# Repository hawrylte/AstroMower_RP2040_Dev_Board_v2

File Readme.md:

# AstroMower RP2040 Dev Board v2
## About
RP2040 Development Board to explore programming capability of Raspberry Pi [RP2040](https://www.raspberrypi.com/products/rp2040/) MCU for use in future projects.

## Hardware
  * 2 Layer PCB with parts populated on both sides

  * Spacing of pin headers is 0.9" to use on standard breadboard.

  * PCB Overall Dimensions 1.05" W X 1.95" L

  * USB-C Interface

  * Resistor and Capacitor sizes are 0603 and 0805 with hand solder footprints

  * Incorporates Neopixel addressable LED

  * 8 MB QSPI Flash

  * All parts ordered through Digi-Key

  * Developed in [KiCad 7.0](https://www.kicad.org/)

  * DRC for Manufacture through [OSHPARK](https://oshpark.com/)

## Software
### ***SOFTWARE UNDER DEVELOPMENT***
### MicroPython
MicroPython firmware for board can be downloaded directly or built from source.

***Instructions for building from source on Debian based system***

Building from source requires MicroPython source. Installation of this mirrors instructions found in Raspberry Pi [Raspberry Pi Pico Python SDK](https://datasheets.raspberrypi.com/pico/raspberry-pi-pico-python-sdk.pdf)

Create *pico* directory
```
mkdir pico
cd pico
```
Then clone the *micropython* git repository
```
git clone https://github.com/micropython/micropython.git --branch master
```
Fetch additional submodules required for a RP2 MCU board
```
cd micropython
make -C port/rp2 submodules
```
To build *micropython* additional tools are required
```
sudo apt update
sudo apt install cmake gcc-arm-none-eabi libnewlib-arm-none-eabi build-essential libstdc++-arm-none-eabi-newlib
```
Bootstrap a special tool for MicroPython builds
```
make -C mpy-cross
```
***Load Board Specific Files for AstroMower Board***

Download *AstroMower RP2040 Dev Board v2* git repository
```
cd ..
git clone https://github.com/hawrylte/AstroMower_RP2040_Dev_Board_v2.git
```
Move specific board files to proper locations in *MicroPython* source files
```
cp -r AstroMower_RP2040_Dev_Board_v2/src/ASTROMOWER_RP2040_DEV_BOARD_V2 micropython/ports/rp2/boards/ASTROMOWER_RP2040_DEV_BOARD_V2
cp -r AstroMower_RP2040_Dev_Board_v2/src/astromower_rp2040_dev_board_v2.h micropython/lib/pico-sdk/src/boards/include/boards/astromower_rp2040_dev_board_v2.h
```
Build the port we need for RP2040 and specify our particular board to be built
```
cd micropython/ports/rp2
make BOARD=ASTROMOWER_RP2040_DEV_BOARD_V2
```
Copy UF2 Firmware from *MicroPython* build directory to *pico* directory
```
cd ../../..
cp micropython/ports/rp2/build-ASTROMOWER_RP2040_DEV_BOARD_V2/firmware.uf2 AstroMower_RP2040_Dev_Board_MicroPython_firmware.uf2
```
### C/C++

***Instructions for setting up PICO-SDK from source on Debian based system***

Setting up the *pico-sdk* mirrors instructions found in Raspberry Pi [Gettting Stated with Raspberry Pi Pico](https://datasheets.raspberrypi.com/pico/getting-started-with-pico.pdf)

Create *pico* directory
```
mkdir pico
cd pico
```
Then clone the *pico-sdk* and the *pico-examples* git repositories
```
git clone http://github.com/raspberrypi/pico-sdk.git --branch master
cd pico-sdk
git submodule update --init
cd ..
git clone http://github.com/raspberrypi/pico-examples.git --branch master
```
To build *pico-examples* additional tools are required
```
sudo apt update
sudo apt install cmake gcc-arm-none-eabi libnewlib-arm-none-eabi build-essentials libstdc++-arm-none-eabi-newlib
```
Download *AstroMower RP2040 Dev Board v2* git repositiry
```
git clone https://github.com/hawrylte/AstroMower_RP2040_Dev_Board_v2.git
```
Move specific board files to proper locations in *pico-sdk* source files
```
cp -r AstroMower_RP2040_Dev_Board_v2/src/astromower_rp2040_dev_board_v2.h pico-sdk/src/boards/include/boards/astromower_rp2040_dev_board_v2.h
```
***Instructions for building Blink example from PICO-EXAMPLES from source on Debian based system***

***AstroMower Dev Board v2 does not have a discrete LED for Blink to run, but this shows the process of building a C/C++ program for the AstroMower Dev Board v2***

Change to *pico-examples* directory and make *build* directory.
```
cd pico-examples
mkdir build
cd buid
```
Set *PICO_SDK_PATH*
```
export PICO-SDK-PATH=../../pico-sdk
```
Prepare cmke build directory and identify board to build program for.
```
cmake .. -DPICO_BOARD=astromower_rp2040_dev_board_v2
cd blink
make -j4
```
*blink.elf* is used by the debugger
*blink.uf2* is the program and can be dragged onto the RP2040 USB Mass Storage Device

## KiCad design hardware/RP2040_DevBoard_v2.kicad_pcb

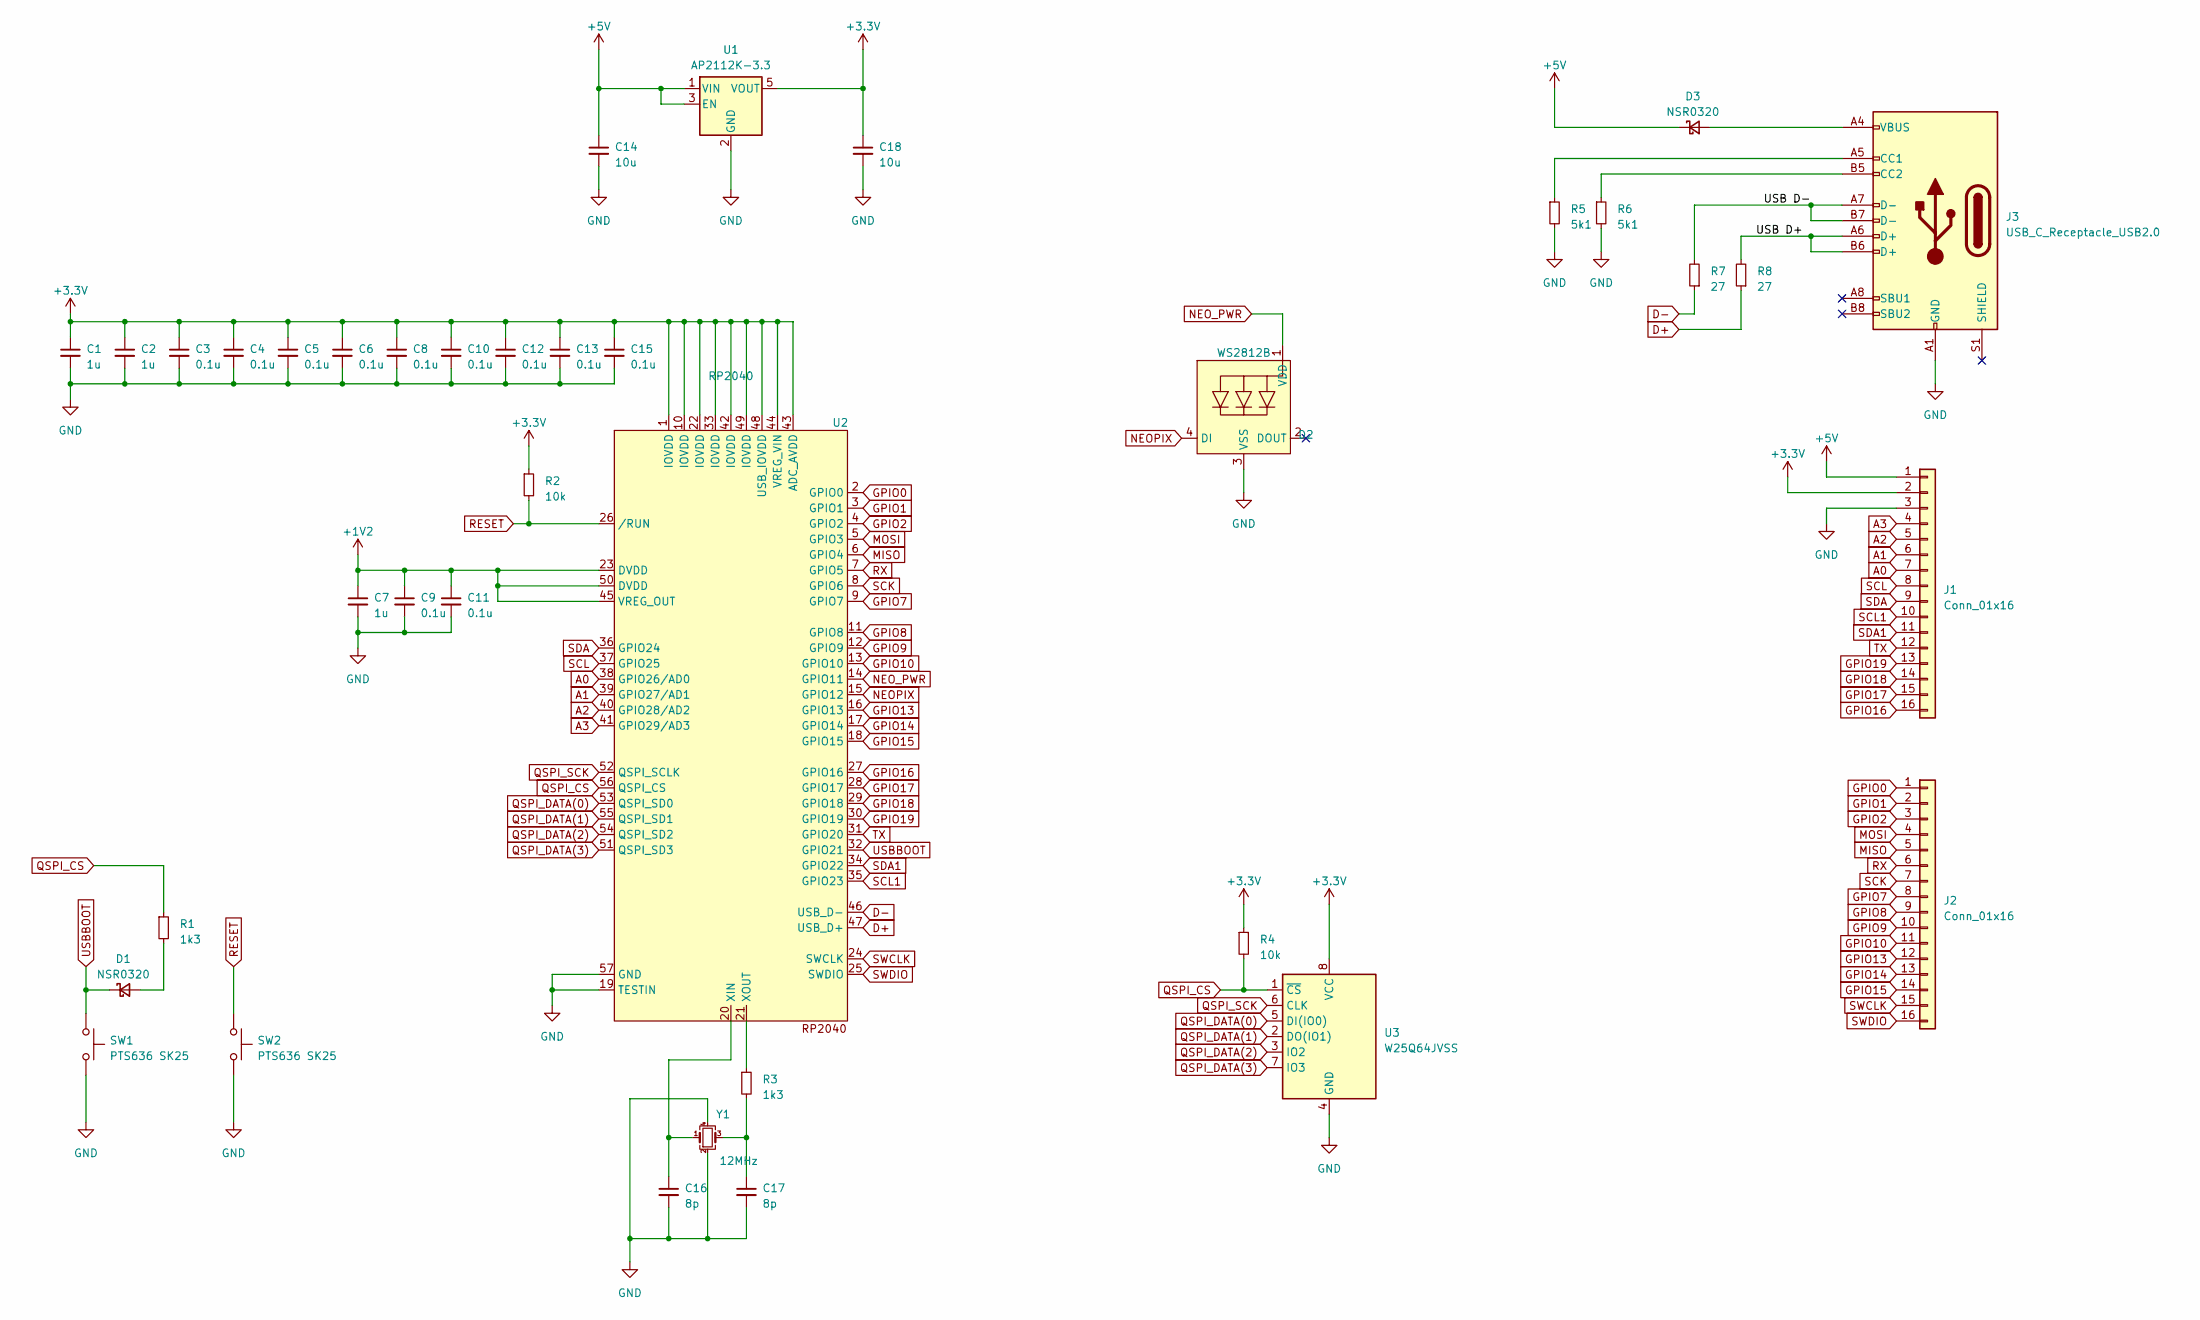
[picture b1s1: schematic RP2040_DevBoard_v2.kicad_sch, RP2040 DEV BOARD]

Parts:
C1, C2, C7: 1u; C_0603_1608Metric_Pad1.08x0.95mm_HandSolder; Mfg PN 0603YC105KAT2A; Digi-Key PN 478-5010-2-ND
C3, C4, C5, C6, C8, C9, C10, C11, C12, C13, C15: 0.1u; C_0603_1608Metric_Pad1.08x0.95mm_HandSolder; Mfg PN 06033C104KAT4A; Digi-Key PN 478-7018-2-ND
C14, C18: 10u; C_0805_2012Metric_Pad1.18x1.45mm_HandSolder; Mfg PN 0805ZC106KAT2A; Digi-Key PN 478-10578-2-ND
C16, C17: 8p; C_0603_1608Metric_Pad1.08x0.95mm_HandSolder; Mfg PN 06031A8R0D4T2A; Digi-Key PN 478-9370-2-ND
D1, D3: NSR0320; D_SOD-323_HandSoldering; Mfg PN NSR0320MW2T3G; Digi-Key PN NSR0320MW2T3GOSTR-ND
D2: WS2812B; Mfg PN COM-16347; Digi-Key PN 1568-COM-16347TR-ND
J1, J2: Conn_01x16; PinHeader_1x16_P2.54mm_Vertical; Mfg PN PH1-16-UA; Digi-Key PN 2057-PH1-16-UA-ND
J3: USB_C_Receptacle_USB2.0; USB_C_Receptacle_GCT_USB4105-xx-A_16P_TopMnt_Horizontal; Mfg PN USB4105-GF-A; Digi-Key PN 2073-USB4105-GF-ATR-ND
R1, R3: 1k3; R_0603_1608Metric_Pad0.98x0.95mm_HandSolder; Mfg PN ERJ-3EKF1301V; Digi-Key PN P1.30KHTR-ND
R2, R4: 10k; R_0603_1608Metric_Pad0.98x0.95mm_HandSolder; Mfg PN ERJ-3EKF1002V; Digi-Key PN P10.0KHTR-ND
R5, R6: 5k1; R_0603_1608Metric_Pad0.98x0.95mm_HandSolder; Mfg PN ERJ-3EKF5101V; Digi-Key PN P5.10KHTR-ND
R7, R8: 27; R_0603_1608Metric_Pad0.98x0.95mm_HandSolder; Mfg PN ERJ-3EKF27R0V; Digi-Key PN P27.0HTR-ND
SW1, SW2: PTS636 SK25; SW_SPST_CK_RS282G05A3; Mfg PN PTS636 SK25 SMTR LFS; Digi-Key PN CKN12322-2-ND
U1: AP2112K-3.3; SOT-23-5; Mfg PN AP2112K-3.3TRG1; Digi-Key PN AP2112K-3.3TRG1DITR-ND
U2: RP2040; QFN-56-1EP_7x7mm_P0.4mm_EP4x4mm; Mfg PN SC0914(13); Digi-Key PN 2648-SC0914(13)TR-ND
U3: W25Q64JVSS; SOIC-8_5.23x5.23mm_P1.27mm; Mfg PN W25Q64JVSSIQ; Digi-Key PN W25Q64JVSSIQ-ND
Y1: 12MHz; Crystal_SMD_3225-4Pin_3.2x2.5mm_HandSoldering; Mfg PN 830108206909; Digi-Key PN 1923-830108206909TR-ND

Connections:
+1V2: C7.1, C9.1, C11.1, U2.23 (DVDD), U2.45 (VREG_OUT), U2.50 (DVDD)
+3.3V: C1.1, C2.1, C3.1, C4.1, C5.1, C6.1, C8.1, C10.1, C12.1, C13.1, C15.1, C18.1, J1.2, R2.1, R4.1, U1.5 (VOUT), U2.1 (IOVDD), U2.10 (IOVDD), U2.22 (IOVDD), U2.33 (IOVDD), U2.42 (IOVDD), U2.43 (ADC_AVDD), U2.44 (VREG_VIN), U2.48 (USB_IOVDD), U2.49 (IOVDD), U3.8 (VCC)
+5V: C14.1, D3.1 (K), J1.1, U1.1 (VIN), U1.3 (EN)
/USB D+: J3.A6 (D+), J3.B6 (D+), R8.2
/USB D-: J3.A7 (D-), J3.B7 (D-), R7.2
A0: J1.7, U2.38 (GPIO26/AD0)
A1: J1.6, U2.39 (GPIO27/AD1)
A2: J1.5, U2.40 (GPIO28/AD2)
A3: J1.4, U2.41 (GPIO29/AD3)
D+: R8.1, U2.47 (USB_D+)
D-: R7.1, U2.46 (USB_D-)
GND: C1.2, C2.2, C3.2, C4.2, C5.2, C6.2, C7.2, C8.2, C9.2, C10.2, C11.2, C12.2, C13.2, C14.2, C15.2, C16.2, C17.2, C18.2, D2.3 (VSS), J1.3, J3.A1 (GND), J3.A12 (GND), J3.B1 (GND), J3.B12 (GND), R5.2, R6.2, SW1.2 (B), SW2.2 (B), U1.2 (GND), U2.19 (TESTIN), U2.57 (GND), U3.4 (GND), Y1.2, Y1.4
GPIO0: J2.1, U2.2 (GPIO0)
GPIO1: J2.2, U2.3 (GPIO1)
GPIO2: J2.3, U2.4 (GPIO2)
GPIO7: J2.8, U2.9 (GPIO7)
GPIO8: J2.9, U2.11 (GPIO8)
GPIO9: J2.10, U2.12 (GPIO9)
GPIO10: J2.11, U2.13 (GPIO10)
GPIO13: J2.12, U2.16 (GPIO13)
GPIO14: J2.13, U2.17 (GPIO14)
GPIO15: J2.14, U2.18 (GPIO15)
GPIO16: J1.16, U2.27 (GPIO16)
GPIO17: J1.15, U2.28 (GPIO17)
GPIO18: J1.14, U2.29 (GPIO18)
GPIO19: J1.13, U2.30 (GPIO19)
MISO: J2.5, U2.6 (GPIO4)
MOSI: J2.4, U2.5 (GPIO3)
NEOPIX: D2.4 (DI), U2.15 (GPIO12)
NEO_PWR: D2.1 (VDD), U2.14 (GPIO11)
unnamed: C17.1, R3.2, Y1.3
unnamed: D1.2 (A), R1.2
unnamed: D3.2 (A), J3.A4 (VBUS), J3.A9 (VBUS), J3.B4 (VBUS), J3.B9 (VBUS)
unnamed: J3.A5 (CC1), R5.1
unnamed: J3.B5 (CC2), R6.1
unnamed: C16.1, U2.20 (XIN), Y1.1
unnamed: R3.1, U2.21 (XOUT)
QSPI_CS: R1.1, R4.2, U2.56 (QSPI_CS), U3.1 (~CS)
QSPI_DATA(0): U2.53 (QSPI_SD0), U3.5 (DI(IO0))
QSPI_DATA(1): U2.55 (QSPI_SD1), U3.2 (DO(IO1))
QSPI_DATA(2): U2.54 (QSPI_SD2), U3.3 (IO2)
QSPI_DATA(3): U2.51 (QSPI_SD3), U3.7 (IO3)
QSPI_SCK: U2.52 (QSPI_SCLK), U3.6 (CLK)
RESET: R2.2, SW2.1 (A), U2.26 (/RUN)
RX: J2.6, U2.7 (GPIO5)
SCK: J2.7, U2.8 (GPIO6)
SCL: J1.8, U2.37 (GPIO25)
SCL1: J1.10, U2.35 (GPIO23)
SDA: J1.9, U2.36 (GPIO24)
SDA1: J1.11, U2.34 (GPIO22)
SWCLK: J2.15, U2.24 (SWCLK)
SWDIO: J2.16, U2.25 (SWDIO)
TX: J1.12, U2.31 (GPIO20)
USBBOOT: D1.1 (K), SW1.1 (A), U2.32 (GPIO21)

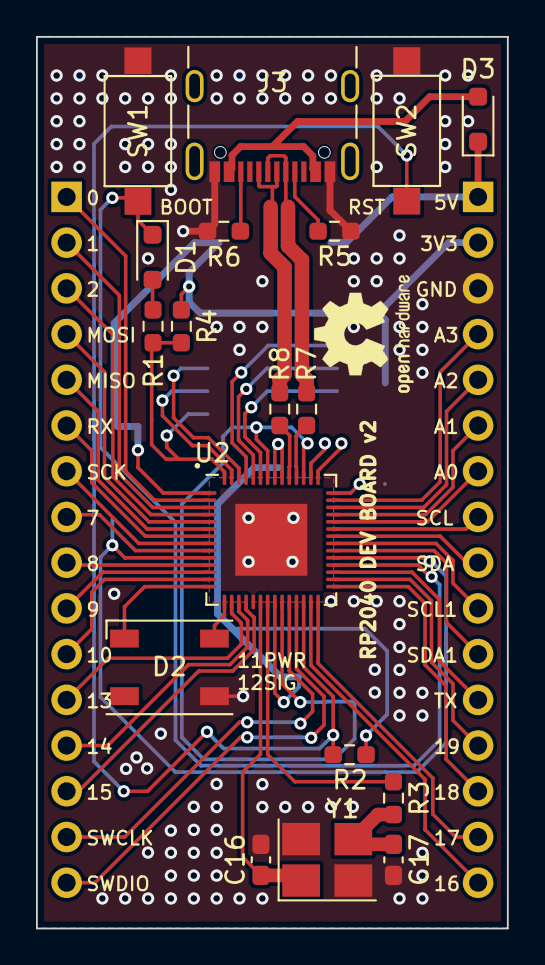
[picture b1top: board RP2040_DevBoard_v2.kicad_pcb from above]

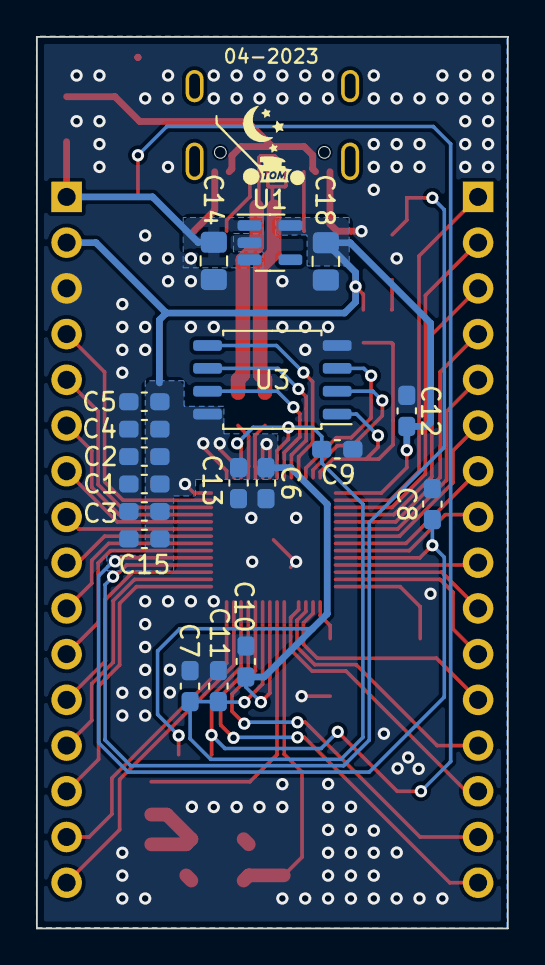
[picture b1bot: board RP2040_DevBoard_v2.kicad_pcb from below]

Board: 2 copper layers, 26.2 x 49.5 mm, 38 parts (20 on the bottom side), 54 nets.

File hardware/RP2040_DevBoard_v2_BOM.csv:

"Copyright 2023 Thomas Hawrylik","","","","","",""
"This source describes Open Hardware and is licensed under the CERN-OHL-S v2 or any later version","","","","","",""
"You may redistribute and modify this source and make products using it under the terms of the CERN-OHL-S v2 (https://ohwr.org/cern ohl s v2.txt).","","","","","",""
"This source is distributed WITHOUT ANY EXPRESS OR IMPLIED WARRANTY, INCLUDING OF MERCHANTABILITY, SATISFACTORY QUALITY AND FITNESS FOR A PARTICULAR PURPOSE.","","","","","",""
"Please see the CERN-OHL-S v2 for applicable conditions.","","","","","",""
"Reference","Value","Footprint","Datasheet","Digi-Key PN","Mfg PN","Qty"
"C1, C2, C7","1u","Capacitor_SMD:C_0603_1608Metric_Pad1.08x0.95mm_HandSolder","https://datasheets.kyocera-avx.com/X7RDielectric.pdf","478-5010-2-ND","0603YC105KAT2A","3"
"C3-C6, C8-C13, C15","0.1u","Capacitor_SMD:C_0603_1608Metric_Pad1.08x0.95mm_HandSolder","https://datasheets.kyocera-avx.com/X7RDielectric.pdf","478-7018-2-ND","06033C104KAT4A","11"
"C14, C18","10u","Capacitor_SMD:C_0805_2012Metric_Pad1.18x1.45mm_HandSolder","https://datasheets.kyocera-avx.com/X7RDielectric.pdf","478-10578-2-ND","0805ZC106KAT2A","2"
"C16, C17","8p","Capacitor_SMD:C_0603_1608Metric_Pad1.08x0.95mm_HandSolder","https://datasheets.kyocera-avx.com/AutoMLCC.pdf","478-9370-2-ND","06031A8R0D4T2A","2"
"D1, D3","NSR0320","Diode_SMD:D_SOD-323_HandSoldering","https://www.onsemi.com/pdf/datasheet/nsr0320mw2t1-d.pdf","NSR0320MW2T3GOSTR-ND","NSR0320MW2T3G","2"
"D2","WS2812B","RP2040_DevBoard:WS2812B","http://cdn.sparkfun.com/datasheets/BreakoutBoards/WS2812B.pdf","1568-COM-16347TR-ND","COM-16347","1"
"J1, J2","Conn_01x16","Connector_PinHeader_2.54mm:PinHeader_1x16_P2.54mm_Vertical","https://app.adam-tech.com/products/download/data_sheet/20160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","2057-PH1-16-UA-ND","PH1-16-UA","2"
"J3","USB_C_Receptacle_USB2.0","Connector_USB:USB_C_Receptacle_GCT_USB4105-xx-A_16P_TopMnt_Horizontal","https://media.digikey.com/pdf/Data%20Sheets/GCT%20PDFs/USB41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","2073-USB4105-GF-ATR-ND","USB4105-GF-A","1"
"R1, R3","1k3","Resistor_SMD:R_0603_1608Metric_Pad0.98x0.95mm_HandSolder","https://industrial.panasonic.com/cdbs/www-data/pdf/RDA0000/A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","P1.30KHTR-ND","ERJ-3EKF1301V","2"
"R2, R4","10k","Resistor_SMD:R_0603_1608Metric_Pad0.98x0.95mm_HandSolder","https://industrial.panasonic.com/cdbs/www-data/pdf/RDA0000/A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","P10.0KHTR-ND","ERJ-3EKF1002V","2"
"R5, R6","5k1","Resistor_SMD:R_0603_1608Metric_Pad0.98x0.95mm_HandSolder","https://industrial.panasonic.com/cdbs/www-data/pdf/RDA0000/A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","P5.10KHTR-ND","ERJ-3EKF5101V","2"
"R7, R8","27","Resistor_SMD:R_0603_1608Metric_Pad0.98x0.95mm_HandSolder","https://industrial.panasonic.com/cdbs/www-data/pdf/RDA0000/A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","P27.0HTR-ND","ERJ-3EKF27R0V","2"
"SW1, SW2","PTS636 SK25","Button_Switch_SMD:SW_SPST_CK_RS282G05A3","https://www.ckswitches.com/media/2779/pts636.pdf","CKN12322-2-ND","PTS636 SK25 SMTR LFS","2"
"U1","AP2112K-3.3","Package_TO_SOT_SMD:SOT-23-5","https://www.diodes.com/assets/Datasheets/AP2112.pdf","AP2112K-3.3TRG1DITR-ND","AP2112K-3.3TRG1","1"
"U2","RP2040","Package_DFN_QFN:QFN-56-1EP_7x7mm_P0.4mm_EP4x4mm","https://datasheets.raspberrypi.com/rp2040/rp2040-datasheet.pdf","2648-SC0914(13)TR-ND","SC0914(13)","1"
"U3","W25Q64JVSS","Package_SO:SOIC-8_5.23x5.23mm_P1.27mm","https://www.winbond.com/resource-files/w25q64jv%20revj%20032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","W25Q64JVSSIQ-ND","W25Q64JVSSIQ","1"
"Y1","12MHz","Crystal:Crystal_SMD_3225-4Pin_3.2x2.5mm_HandSoldering","https://www.we-online.com/catalog/datasheet/830108206909.pdf","1923-830108206909TR-ND","830108206909","1"

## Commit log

2023-05-04 Create license.txt
    CERN OHL v2 Strongly Reciprocal
2023-05-04 Rename RP2040_DevBoard.bak to RP2040_DevBoard.bak
2023-05-04 Rename WS2812B.kicad_mod to WS2812B.kicad_mod
2023-05-04 Rename RP2040_DevBoard.kicad_sym to RP2040_DevBoard.kicad_sym
2023-05-04 Rename RP2040_DevBoard_v2.kicad_pcb to RP2040_DevBoard_v2.kicad_pcb
2023-05-04 Rename RP2040_DevBoard_v2.kicad_prl to RP2040_DevBoard_v2.kicad_prl
2023-05-04 Rename RP2040_DevBoard_v2.kicad_pro to RP2040_DevBoard_v2.kicad_pro
2023-05-04 Create r
2023-05-04 Create _temp
2023-05-07 Create CERN-OHL-S V2
2023-05-07 Create MIT
2023-05-07 Rename RP2040_DevBoard_v2_kicad.sch.license to .RP2040_DevBoard_v2_kicad_sch.license
2023-05-07 Rename .RP2040_DevBoard_v2_kicad_sch.license to RP2040_DevBoard_v2_kicad_sch.license
2023-05-07 Rename RP2040_DevBoard_v2_kicad_sch.license to RP2040_DevBoard_v2.kicad_sch.license
